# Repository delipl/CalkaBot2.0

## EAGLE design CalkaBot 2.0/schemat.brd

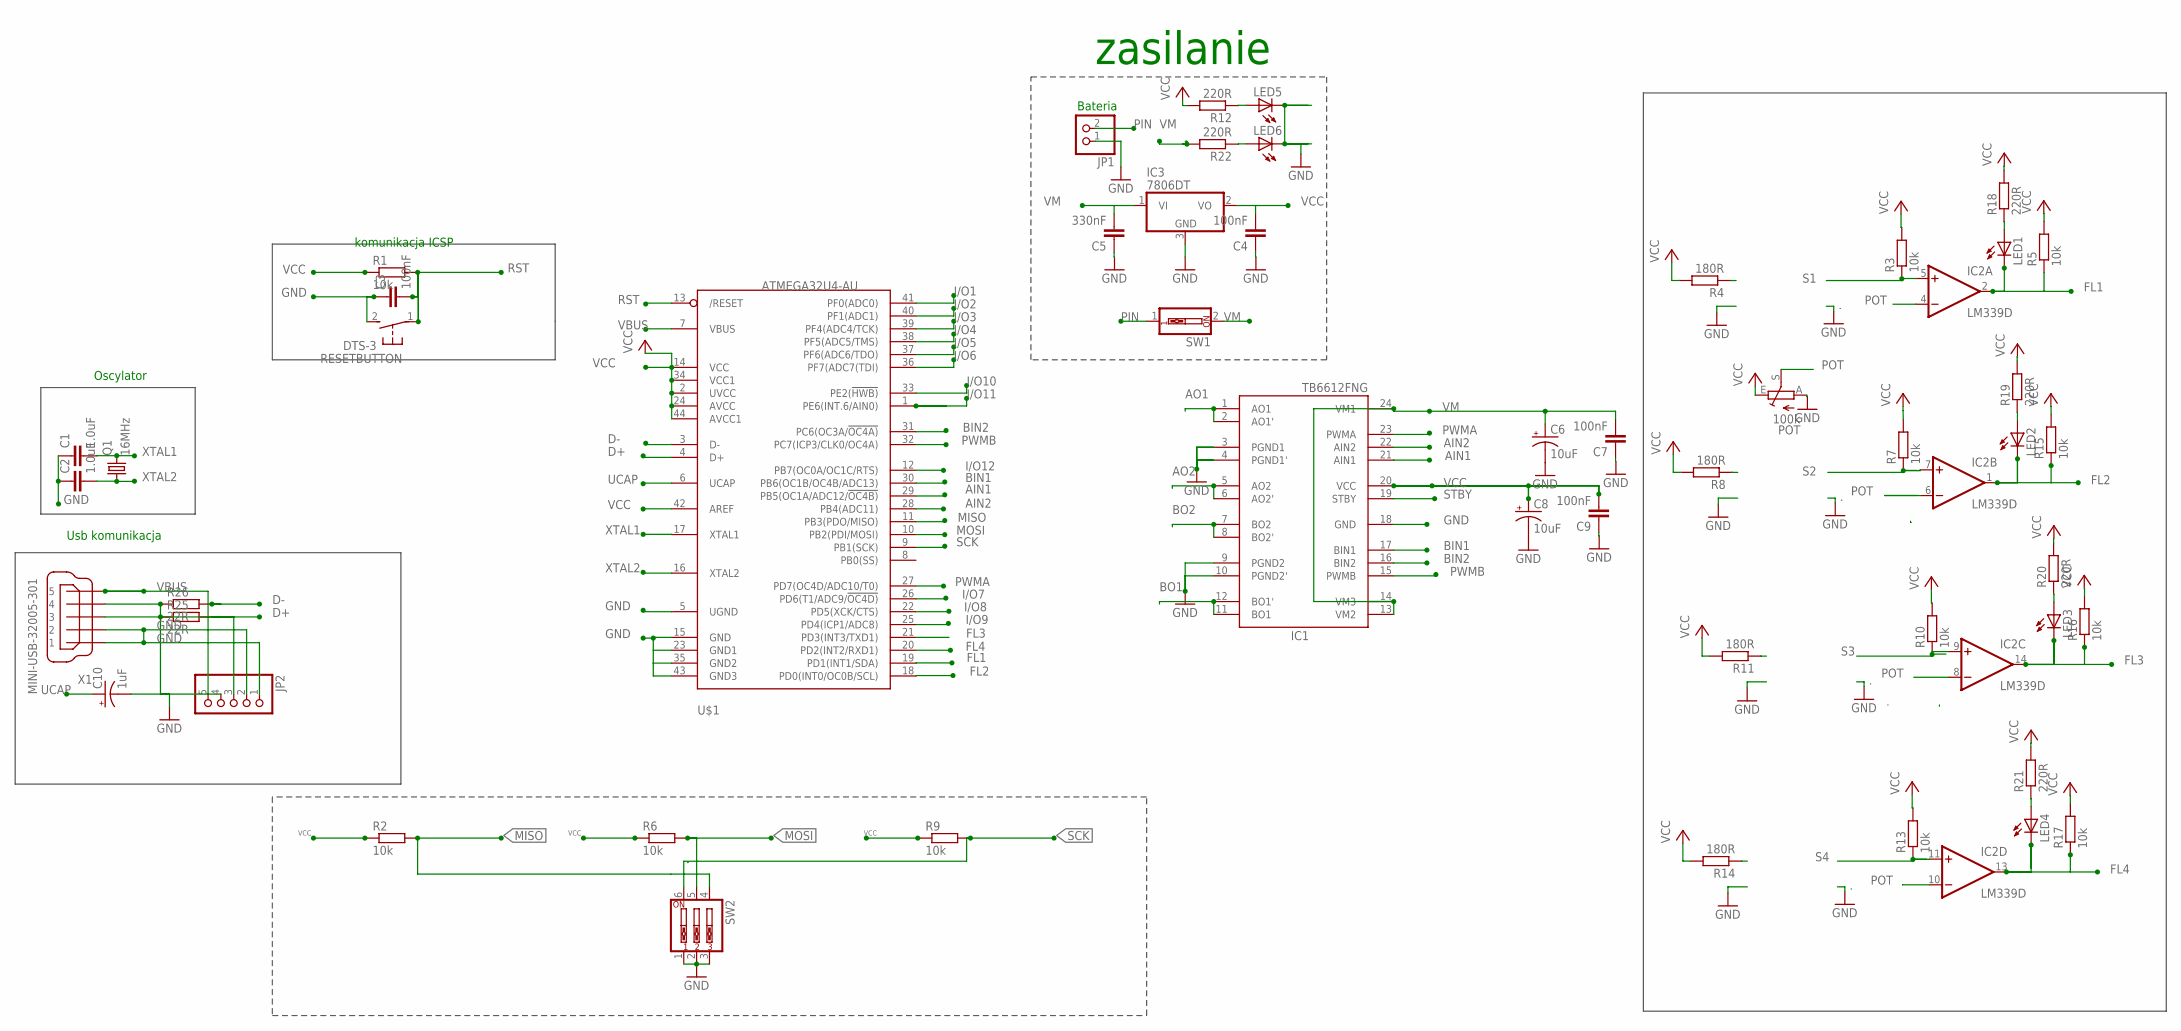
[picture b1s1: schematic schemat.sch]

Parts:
C1, C2: 1.0uF; C0805
C3, C4, C7, C9: 100nF; C0805
C5: 330nF; C0805
C6, C8: 10uF; UD-4X5,8_NICHICON
C10: 1uF; UD-4X5,8_NICHICON
IC1: TB6612FNG; SSOP24
IC2: LM339D; SO14
IC3: 7806DT; TO252
JP1: PINHD-1X2; 1X02
JP2: PINHD-1X5; 1X05
LED1, LED2, LED3, LED4, LED5, LED6: LEDCHIP-LED0805; CHIP-LED0805
POT: 100k; CA6V
Q1: 16MHz; CSM-7X-DU
R1, R2, R3, R5, R6, R7, R9, R10, R13, R15, R16, R17: 10k; R0805
R4, R8, R11, R14: 180R; R0805
R12, R18, R19, R20, R21, R22: 220R; R0805
R25, R26: 22R; R0805
RESETBUTTON: DTS-3
SW1: SW_DIP-1; EDG-01
SW2: SW_DIP-3; EDG-03
U$1: ATMEGA32U4-AU; TQFP44
X1: MINI-USB-32005-301; 32005-301

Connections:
AIN1: IC1.21 (AIN1), U$1.29 (PB5(OC1A/ADC12/!OC4B))
AIN2: IC1.22 (AIN2), U$1.28 (PB4(ADC11))
AO1: IC1.1 (AO1), IC1.2 (AO1')
AO2: IC1.5 (AO2), IC1.6 (AO2')
BIN1: IC1.17 (BIN1), U$1.30 (PB6(OC1B/OC4B/ADC13))
BIN2: IC1.16 (BIN2), U$1.31 (PC6(OC3A/!OC4A))
BO1: IC1.11 (BO1), IC1.12 (BO1')
BO2: IC1.7 (BO2), IC1.8 (BO2')
D+: R25.2, U$1.4 (D+)
D-: R26.2, U$1.3 (D-)
FL1: IC2.2 (OUT), LED1.C, R5.1, U$1.19 (PD1(INT1/SDA))
FL2: IC2.1 (OUT), LED2.C, R15.1, U$1.18 (PD0(INT0/OC0B/SCL))
FL3: IC2.14 (OUT), LED3.C, R16.1, U$1.21 (PD3(INT3/TXD1))
FL4: IC2.13 (OUT), LED4.C, R17.1, U$1.20 (PD2(INT2/RXD1))
GND: C1.1, C2.1, C3.1, C4.1, C5.1, C6.-, C7.1, C8.-, C9.1, C10.-, IC1.3 (PGND1), IC1.4 (PGND1'), IC1.9 (PGND2), IC1.10 (PGND2'), IC1.18 (GND), IC2.12 (GND), IC3.3 (GND), JP1.1, JP2.1, JP2.2, LED5.C, LED6.C, POT.A, RESETBUTTON.2, SW2.1, SW2.2, SW2.3, U$1.5 (UGND), U$1.15 (GND), U$1.23 (GND1), U$1.35 (GND2), U$1.43 (GND3), X1.1, X1.2
I/O1: U$1.41 (PF0(ADC0))
I/O2: U$1.40 (PF1(ADC1))
I/O3: U$1.39 (PF4(ADC4/TCK))
I/O4: U$1.38 (PF5(ADC5/TMS))
I/O5: U$1.37 (PF6(ADC6/TDO))
I/O6: U$1.36 (PF7(ADC7(TDI))
I/O7: U$1.26 (PD6(T1/ADC9/!OC4D))
I/O8: U$1.22 (PD5(XCK/CTS))
I/O9: U$1.25 (PD4(ICP1/ADC8))
I/O10: U$1.33 (PE2(!HWB))
I/O11: U$1.1 (PE6(INT.6/AIN0))
I/O12: U$1.12 (PB7(OC0A/OC1C/RTS))
MISO: R2.2, SW2.4, U$1.11 (PB3(PDO/MISO))
MOSI: R6.2, SW2.5, U$1.10 (PB2(PDI/MOSI))
unnamed: LED5.A, R12.1
unnamed: LED6.A, R22.1
unnamed: JP2.3, R25.1, X1.3
unnamed: LED1.A, R18.1
unnamed: LED2.A, R19.1
unnamed: LED3.A, R20.1
unnamed: LED4.A, R21.1
unnamed: JP2.4, R26.1, X1.4
PIN: JP1.2, SW1.1
POT: IC2.4 (-IN), IC2.6 (-IN), IC2.8 (-IN), IC2.10 (-IN), POT.S
PWMA: IC1.23 (PWMA), U$1.27 (PD7(OC4D/ADC10/T0))
PWMB: IC1.15 (PWMB), U$1.32 (PC7(ICP3/CLK0/OC4A))
RST: C3.2, R1.2, RESETBUTTON.1, U$1.13 (/RESET)
S1: IC2.5 (+IN), R3.1
S2: IC2.7 (+IN), R7.1
S3: IC2.9 (+IN), R10.1
S4: IC2.11 (+IN), R13.1
SCK: R9.2, SW2.6, U$1.9 (PB1(SCK))
STBY: IC1.19 (STBY)
UCAP: C10.+, U$1.6 (UCAP)
VBUS: JP2.5, U$1.7 (VBUS), X1.5
VCC: C4.2, C8.+, C9.2, IC1.20 (VCC), IC2.3 (V+), IC3.2 (VO), POT.E, R1.1, R2.1, R3.2, R4.2, R5.2, R6.1, R7.2, R8.2, R9.1, R10.2, R11.2, R12.2, R13.2, R14.2, R15.2, R16.2, R17.2, R18.2, R19.2, R20.2, R21.2, U$1.2 (UVCC), U$1.14 (VCC), U$1.24 (AVCC), U$1.34 (VCC1), U$1.42 (AREF), U$1.44 (AVCC1)
VM: C5.2, C6.+, C7.2, IC1.13 (VM2), IC1.14 (VM3), IC1.24 (VM1), IC3.1 (VI), R22.2, SW1.2
XTAL1: C1.2, Q1.2, U$1.17 (XTAL1)
XTAL2: C2.2, Q1.1, U$1.16 (XTAL2)

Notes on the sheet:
Oscylator
Usb komunikacja
komunikacja ICSP
Bateria
zasilanie

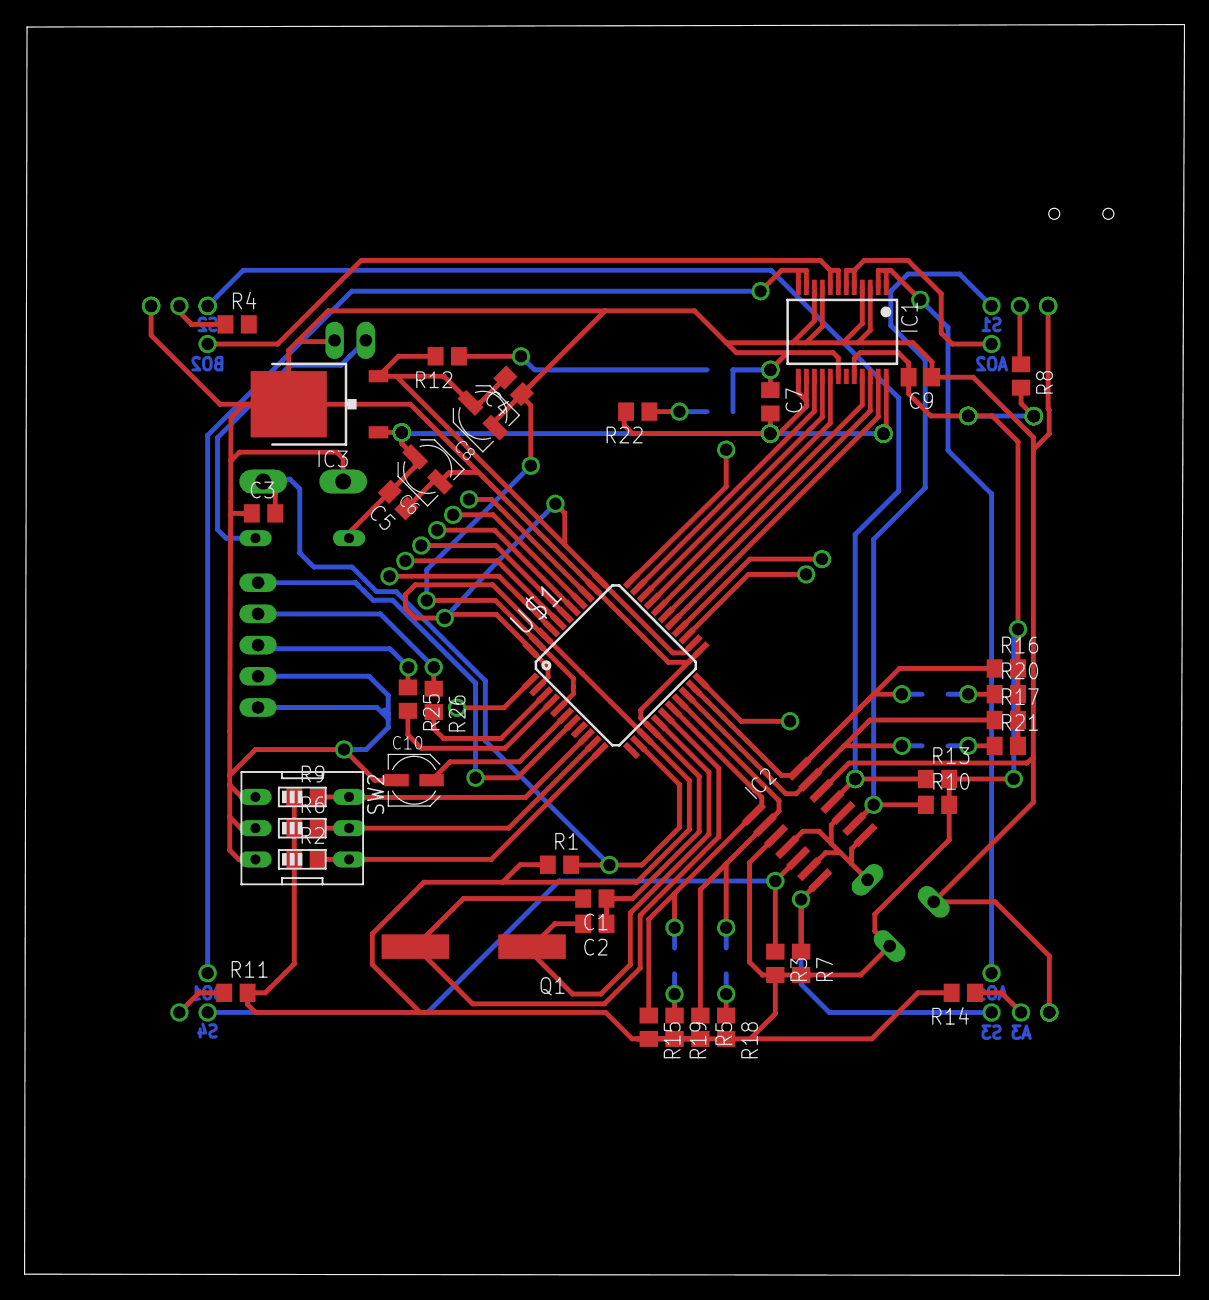
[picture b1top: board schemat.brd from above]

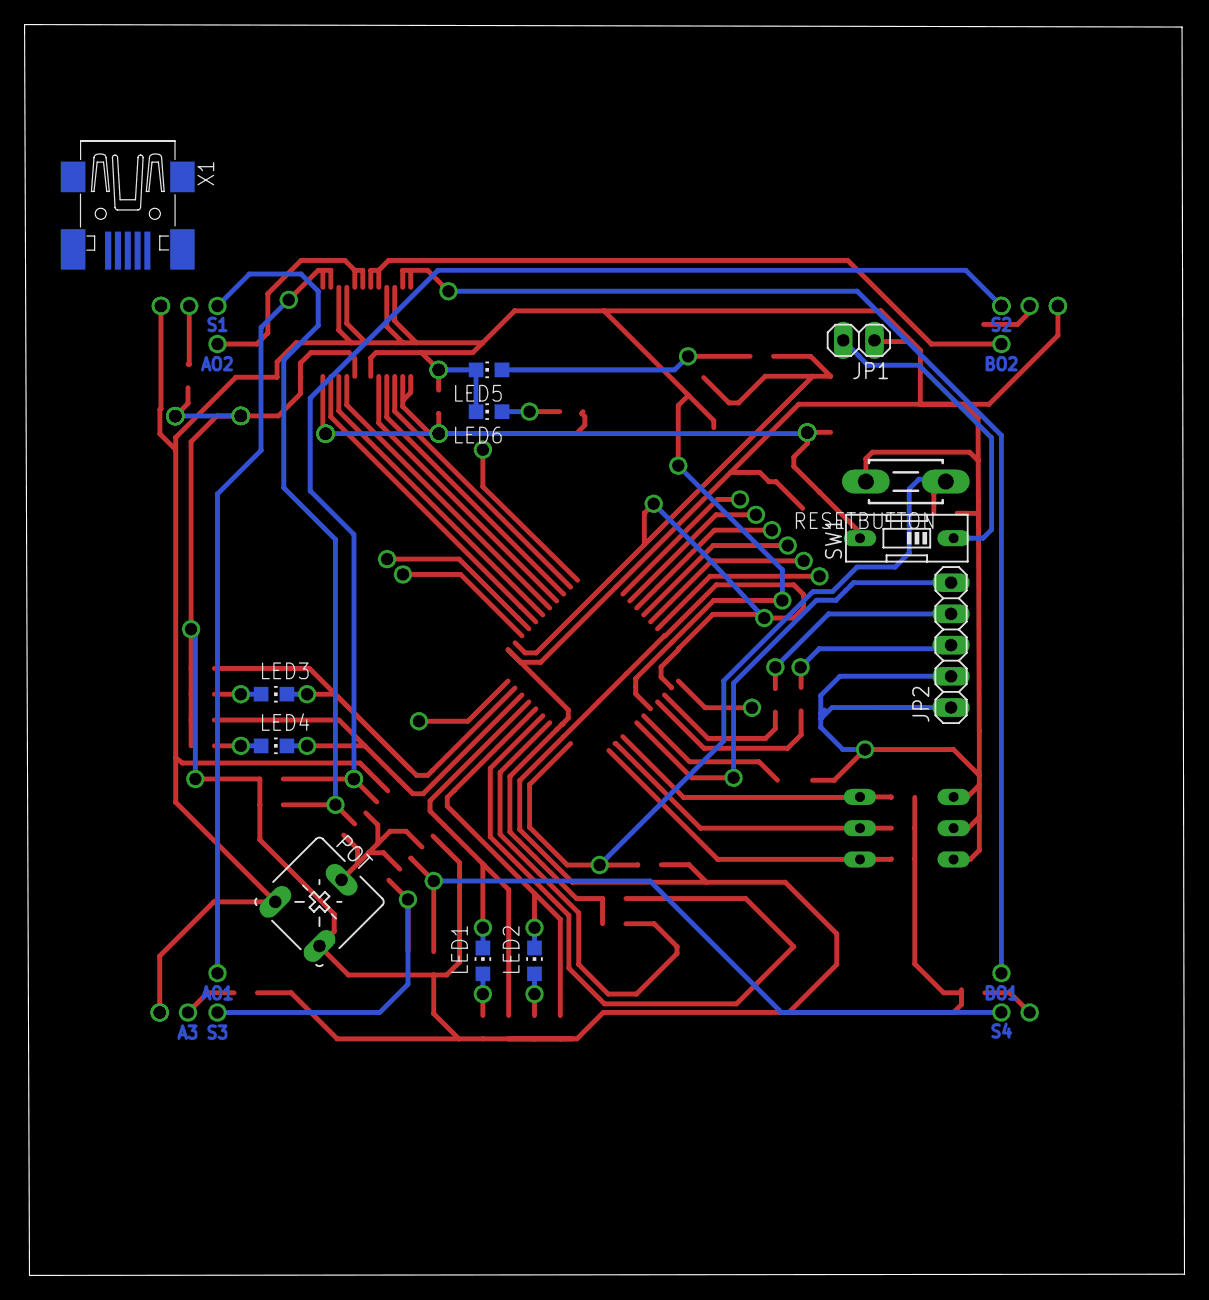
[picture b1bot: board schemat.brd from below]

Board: 2 copper layers, 94.4 x 101.8 mm, 52 parts (12 on the bottom side), 41 nets.

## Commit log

2018-11-21 zmiana przycisków
2018-11-21 połączono wszystkie vcc i gnd
2018-11-21 test
2018-11-21 powrót do normalnego działania
2018-11-21 usunąłem
2018-11-21 cos sie dodoał
2018-11-21 czary mary?
2018-11-22 dzikość
